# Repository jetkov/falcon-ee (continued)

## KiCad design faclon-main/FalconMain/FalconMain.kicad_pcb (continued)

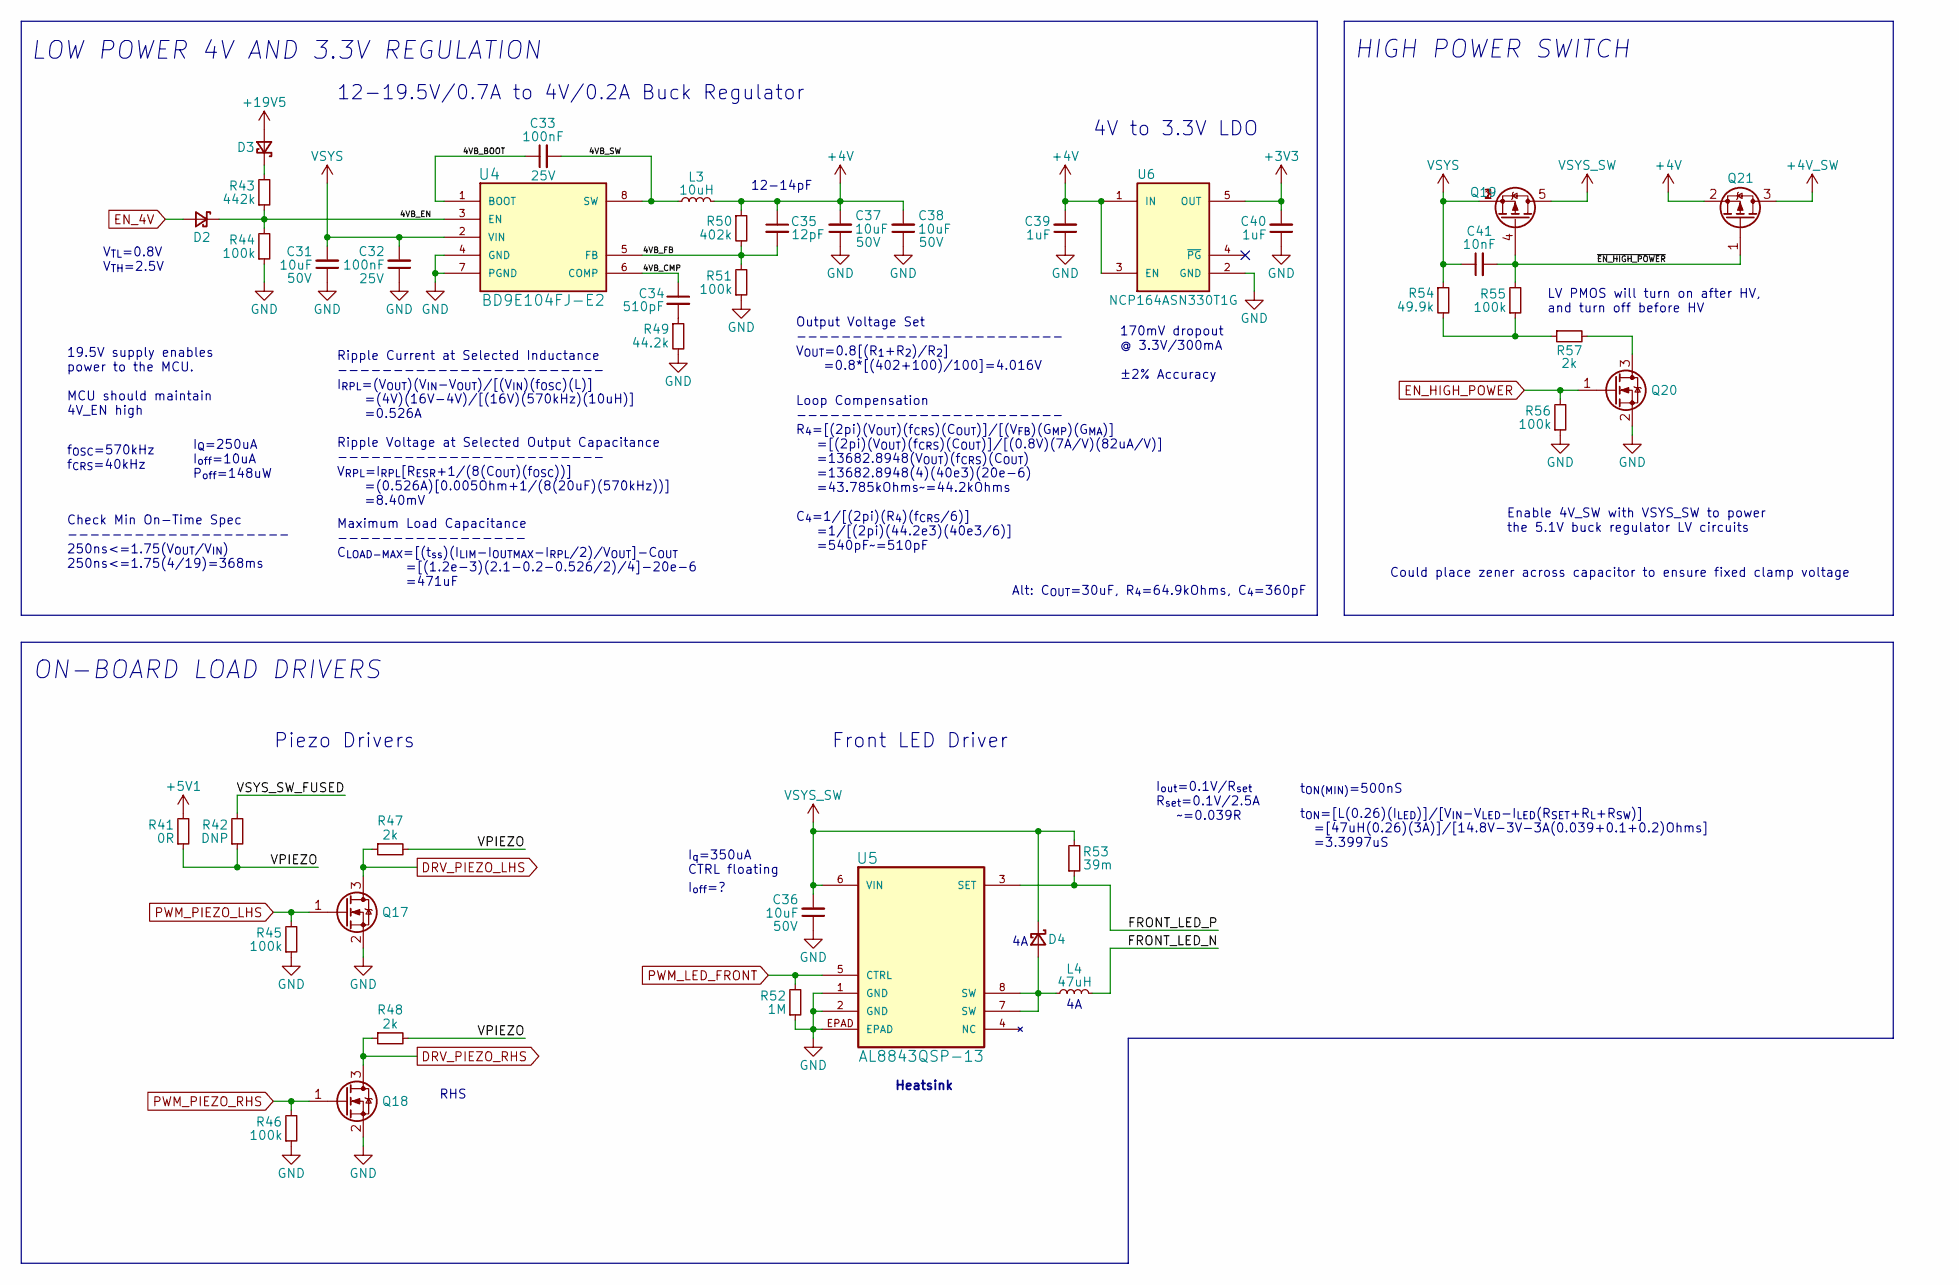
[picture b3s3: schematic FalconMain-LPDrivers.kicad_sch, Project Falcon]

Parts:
C31, C36, C37, C38: 10uF; C_1210_3225Metric; Tolerance 10%; Voltage 50V; Part Number CGA6P3X7S1H106K250AB
C32, C33: 100nF; C_0402_1005Metric; Tolerance 10%; Voltage 25V; Part Number GRM155R71E104KE14D
C34: 510pF; C_0402_1005Metric; Tolerance 5%; Voltage 50V; Part Number GRM1555C1H511JA01D
C35: 12pF; C_0402_1005Metric; Tolerance 5%; Voltage 50V; Part Number GCM1555C1H120JA16D
C39, C40: 1uF; C_0603_1608Metric; Tolerance 10%; Voltage 25V; Part Number CGA3E1X7R1E105K080AC
C41: 10nF; C_0402_1005Metric; Tolerance 10%; Voltage 50V; Part Number 885012205067
D2, D3: 500mA; SC-76-SOD-323_USC_TSB; Voltage 30V; Part Number CUS551V30,H3F
D4: 20A; TO-252-2-3_DPAK_ST; Voltage 45V; Part Number FERD2045SB-TR
L3: 10uH; L_1008_2520Metric; Tolerance 10%; Part Number LBC2518T100K
L4: 47uH; AMDLA1306S; Tolerance 20%; Part Number AMDLA1306S-470MT
Q17, Q18, Q20: Q_NMOS_GSD; SOT-323_SC-70; Voltage 20Vgs/60Vds/1Vth; Part Number DMN61D9UWQ-13
Q19: Q_PMOS_LFPAK; LFPACK56-S08_SOT669_NXP; Voltage 20Vgs/30Vds/3Vth; Part Number BUK6Y19-30PX
Q21: Q_PMOS_GSD; SC-96_TSMT3_ROM; Voltage 20Vgs/30Vds/2.5Vth; Part Number RQ5E025ATTCL
R41: 0R; R_0402_1005Metric; Tolerance Jumper; Part Number RMCF0402ZT0R00
R42: DNP; R_0402_1005Metric; Tolerance Jumper; Part Number RMCF0402ZT0R00
R43: 442k; R_0402_1005Metric; Tolerance 1%; Part Number RMCF0402FT442K
R44, R45, R46, R51, R55, R56: 100k; R_0402_1005Metric; Tolerance 1%; Part Number RC0402FR-13100KL
R47, R48, R57: 2k; R_0402_1005Metric; Tolerance 1%; Part Number RMCF0402FT2K00
R49: 44.2k; R_0402_1005Metric; Tolerance 1%; Part Number RMCF0402FT44K2
R50: 402k; R_0402_1005Metric; Tolerance 1%; Part Number RMCF0402FT402K
R52: 1M; R_0402_1005Metric; Tolerance 1%; Part Number RMCF0402FT1M00
R53: 39m; R_1206_3216Metric; Tolerance 1%; Part Number KRL1632E-M-R039-F-T5
R54: 49.9k; R_0402_1005Metric; Tolerance 1%; Part Number RMCF0402FT49K9
U4: BD9E104FJ-E2; 8-SOIC_8-SOP-J_ROHM; Part Number BD9E104FJ-E2
U5: AL8843QSP-13; 8-SOIC_SO-8EP_DIO; Part Number AL8843QSP-13
U6: NCP164ASN330T1G; SOT-23-5_TSOP−5_ON; Part Number NCP164ASN330T1G

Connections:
+3V3: C40.2, U6.5 (OUT); also elsewhere on the board
+4V: C35.1, C37.2, C38.2, C39.2, L3.2, Q21.2 (S), R50.1, U6.1 (IN), U6.3 (EN)
+4V_SW: Q21.3 (D); also elsewhere on the board
+5V1: R41.2; also elsewhere on the board
+19V5: D3.2 (A); also elsewhere on the board
/Low Power and Drivers/4VB_BOOT: C33.1, U4.1 (BOOT)
/Low Power and Drivers/4VB_CMP: C34.1, U4.6 (COMP)
/Low Power and Drivers/4VB_EN: D2.1 (K), R43.1, R44.2, U4.3 (EN)
/Low Power and Drivers/4VB_FB: C35.2, R50.2, R51.2, U4.5 (FB)
/Low Power and Drivers/4VB_SW: C33.2, L3.1, U4.8 (SW)
/Low Power and Drivers/FRONT_LED_N: L4.2
/Low Power and Drivers/FRONT_LED_P: R53.1, U5.3 (SET)
/Low Power and Drivers/VPIEZO: R41.1, R42.1, R47.2, R48.2
/Low Power and Drivers/VSYS_SW_FUSED: R42.2
/Low Power and Drivers/~EN_HIGH_POWER: C41.2, Q19.4 (G), Q21.1 (G), R55.2
DRV_PIEZO_LHS: Q17.3 (D), R47.1; also elsewhere on the board
DRV_PIEZO_RHS: Q18.3 (D), R48.1; also elsewhere on the board
EN_4V: D2.2 (A); also elsewhere on the board
EN_HIGH_POWER: Q20.1 (G), R56.2; also elsewhere on the board
GND: C31.1, C32.1, C36.1, C37.1, C38.1, C39.1, C40.1, Q17.2 (S), Q18.2 (S), Q20.2 (S), R44.1, R45.1, R46.1, R49.2, R51.1, R52.1, R56.1, U4.4 (GND), U4.7 (PGND), U5.1 (GND), U5.2 (GND), U5.EPAD, U6.2 (GND); also elsewhere on the board
unnamed: C34.2, R49.1
unnamed: D3.1 (K), R43.2
unnamed: D4.1 (A), D4.2 (A), L4.1, U5.7 (SW), U5.8 (SW)
unnamed: Q20.3 (D), R57.2
unnamed: R54.2, R55.1, R57.1
PWM_LED_FRONT: R52.2, U5.5 (CTRL); also elsewhere on the board
PWM_PIEZO_LHS: Q17.1 (G), R45.2; also elsewhere on the board
PWM_PIEZO_RHS: Q18.1 (G), R46.2; also elsewhere on the board
VSYS: C31.2, C32.2, C41.1, Q19.1 (S), Q19.2 (S), Q19.3 (S), R54.1, U4.2 (VIN); also elsewhere on the board
VSYS_SW: C36.2, D4.3 (K), Q19.5 (D), R53.2, U5.6 (VIN); also elsewhere on the board

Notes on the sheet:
I_{Q}=250uA I_{off}=10uA P_{off}=148uW
Loop Compensation ------------------------ R_{4}=[(2pi)(V_{OUT})(f_{CRS})(C_{OUT})]/[(V_{FB})(G_{MP})(G_{MA})] =[(2pi)(V_{OUT})(f_{CRS})(C_{OUT})]/[(0.8V)(7A/V)(82uA/V)] =13682.8948(V_{OUT})(f_{CRS})(C_{OUT}) =13682.8948(4)(40e3)(20e-6) =43.785kOhms~=44.2kOhms C_{4}=1/[(2pi)(R_{4})(f_{CRS}/6)] =1/[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
HIGH POWER SWITCH
Piezo Drivers
4V to 3.3V LDO
19.5V supply enables power to the MCU. MCU should maintain 4V_EN high
f_{OSC}=570kHz f_{CRS}=40kHz
Maximum Load Capacitance ----------------- C_{LOAD-MAX}=[(t_{ss})(I_{LIM}-I_{OUTMAX}-I_{RPL}/2)/V_{OUT}]-C_{OUT} =[(1.2e-3)(2.1-0.2-0.526/2)/4]-20e-6 =471uF
Ripple Current at Selected Inductance ------------------------ I_{RPL}=(V_{OUT})(V_{IN}-V_{OUT})/[(V_{IN})(f_{OSC})(L)] =(4V)(16V-4V)/[(16V)(570kHz)(10uH)] =0.526A Ripple Voltage at Selected Output Capacitance ------------------------ V_{RPL}=I_{RPL}[R_{ESR}+1/(8(C_{OUT})(f_{OSC}))] =(0.526A)[0.005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
Alt: C_{OUT}=30uF, R_{4}=64.9kOhms, C_{4}=360pF
LV PMOS will turn on after HV, and turn off before HV
Front LED Driver
I_{out}=0.1V/R_{set} R_{set}=0.1V/2.5A ~=0.039R
12-19.5V/0.7A to 4V/0.2A Buck Regulator
12-14pF
RHS
LOW POWER 4V AND 3.3V REGULATION
I_{q}=350uA CTRL floating
Output Voltage Set ------------------------ V_{OUT}=0.8[(R_{1}+R_{2})/R_{2}] =0.8*[(402+100)/100]=4.016V
t_{ON(MIN)}=500nS
I_{off}=?
Could place zener across capacitor to ensure fixed clamp voltage
Enable 4V_SW with VSYS_SW to power the 5.1V buck regulator LV circuits
170mV dropout @ 3.3V/300mA ±2% Accuracy
Check Min On-Time Spec -------------------- 250ns<=1.75(V_{OUT}/V_{IN}) 250ns<=1.75(4/19)=368ms
ON-BOARD LOAD DRIVERS
Heatsink
t_{ON}=[L(0.26)(I_{LED})]/[V_{IN}-V_{LED}-I_{LED}(R_{SET}+R_{L}+R_{SW})] =[47uH(0.26)(3A)]/[14.8V-3V-3A(0.039+0.1+0.2)Ohms] =3.3997uS
V_{TL}=0.8V V_{TH}=2.5V

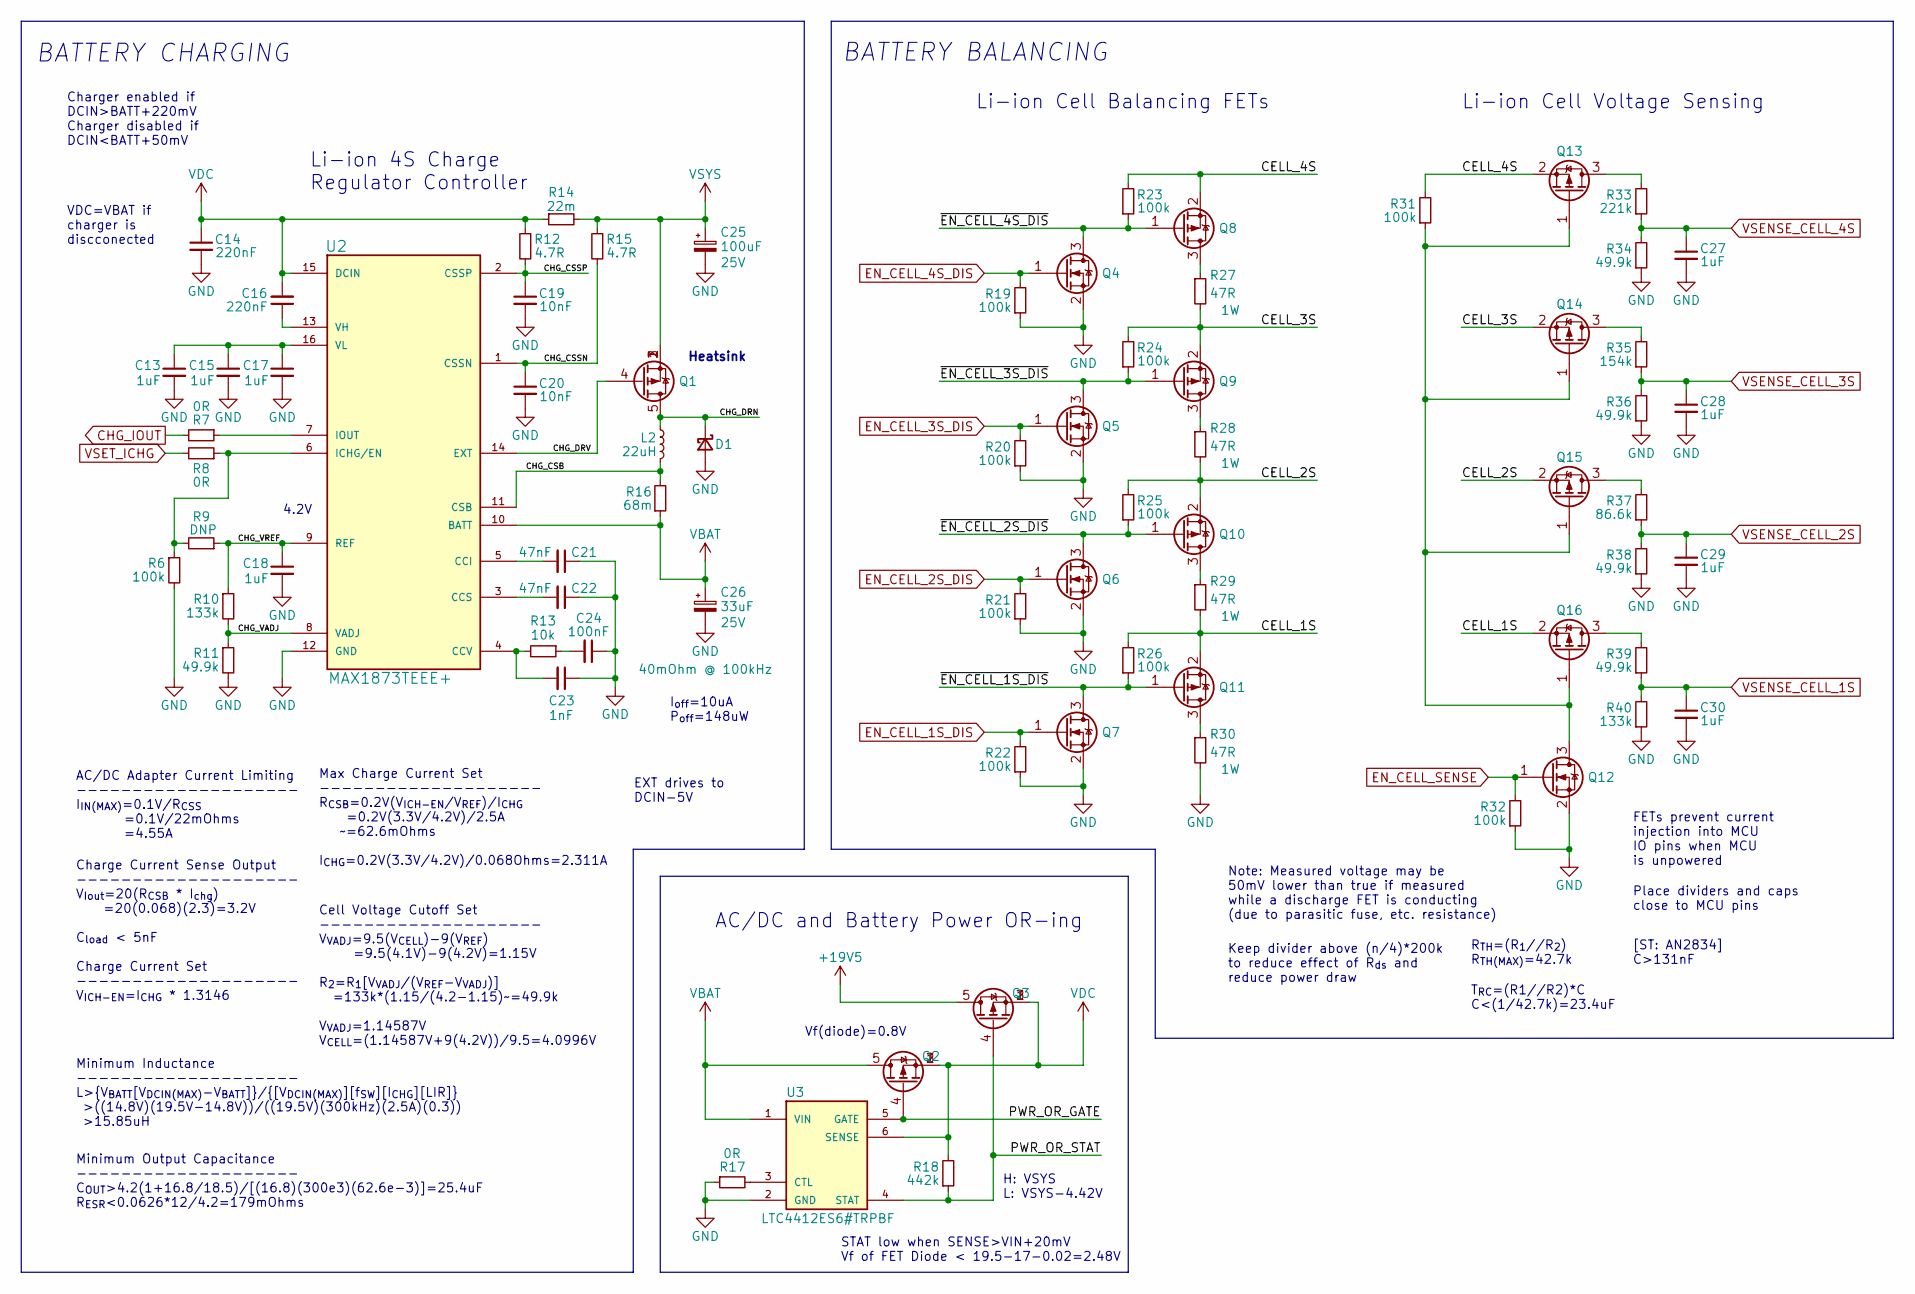
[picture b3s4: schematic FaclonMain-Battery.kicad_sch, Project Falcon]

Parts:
C13, C15, C17, C18, C27, C28, C29, C30: 1uF; C_0603_1608Metric; Tolerance 10%; Voltage 25V; Part Number CGA3E1X7R1E105K080AC
C14, C16: 220nF; C_0603_1608Metric; Tolerance 10%; Voltage 50V; Part Number C1608X7R1H224K080AB
C19, C20: 10nF; C_0402_1005Metric; Tolerance 10%; Voltage 50V; Part Number 885012205067
C21, C22: 47nF; C_0402_1005Metric; Tolerance 10%; Voltage 50V; Part Number GRM155R71H473KE14D
C23: 1nF; C_0402_1005Metric; Tolerance 10%; Voltage 50V; Part Number 885012205061
C24: 100nF; C_0402_1005Metric; Tolerance 10%; Voltage 25V; Part Number GRM155R71E104KE14D
C25: 100uF; CP_Radial_D8.0mm_P3.50mm; Tolerance 20%; Voltage 25V; Part Number A759KS107M1EAAE025
C26: 33uF; CP_Radial_D6.3mm_P2.50mm; Tolerance 20%; Voltage 25V; Part Number A758EK336M1EAAE040
D1: 20A; TO-252-2-3_DPAK_ST; Voltage 45V; Part Number FERD2045SB-TR
L2: 22uH; DR125-220-R_Handsolder; Tolerance 20%; Part Number DR125-220-R
Q1, Q2, Q3: Q_PMOS_LFPAK; LFPACK56-S08_SOT669_NXP; Voltage 20Vgs/30Vds/3Vth; Part Number BUK6Y19-30PX
Q4, Q5, Q6, Q7, Q12: Q_NMOS_GSD; SOT-323_SC-70; Voltage 20Vgs/60Vds/1Vth; Part Number DMN61D9UWQ-13
Q8, Q9, Q10, Q11, Q13, Q14, Q15, Q16: Q_PMOS_GSD; SC-96_TSMT3_ROM; Voltage 20Vgs/30Vds/2.5Vth; Part Number RQ5E025ATTCL
R6, R19, R20, R21, R22, R23, R24, R25, R26, R31, R32: 100k; R_0402_1005Metric; Tolerance 1%; Part Number RC0402FR-13100KL
R7, R8, R17: 0R; R_0402_1005Metric; Tolerance Jumper; Part Number RMCF0402ZT0R00
R9: DNP; R_0402_1005Metric; Tolerance 1%; Part Number RMCF0402FT27K4
R10, R40: 133k; R_0402_1005Metric; Tolerance 1%; Part Number CR0402-FX-1333GLF
R11, R34, R36, R38, R39: 49.9k; R_0402_1005Metric; Tolerance 1%; Part Number RMCF0402FT49K9
R12, R15: 4.7R; R_0402_1005Metric; Tolerance 1%; Part Number RMCF0402FT4R70
R13: 10k; R_0402_1005Metric; Tolerance 1%; Part Number RMCF0402FT10K0
R14: 22m; R_1206_3216Metric; Tolerance 1%; Part Number KRL1632E-M-R022-F-T5
R16: 68m; R_0612_1632Metric; Tolerance 1%; Part Number LTR18EZPFSR068
R18: 442k; R_0402_1005Metric; Tolerance 1%; Part Number RMCF0402FT442K
R27, R28, R29, R30: 47R; R_2512_6332Metric; Tolerance 5%; Part Number RMCF2512JT47R0
R33: 221k; R_0402_1005Metric; Tolerance 1%; Part Number RMCF0402FT221K
R35: 154k; R_0402_1005Metric; Tolerance 1%; Part Number RMCF0402FT154K
R37: 86.6k; R_0402_1005Metric; Tolerance 1%; Part Number RMCF0402FT86K6
U2: MAX1873TEEE+; 16-SSOP_16-QSOP_MAX; Part Number MAX1873TEEE+
U3: LTC4412ES6#TRPBF; SOT-23-6_TSOT-23-6_LT; Part Number LTC4412ES6#TRPBF

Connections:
+19V5: Q3.5 (D); also elsewhere on the board
/Battery/CELL_1S: Q11.2 (S), Q16.2 (S), R26.2, R29.2
/Battery/CELL_2S: Q10.2 (S), Q15.2 (S), R25.2, R28.2
/Battery/CELL_3S: Q9.2 (S), Q14.2 (S), R24.2, R27.2
/Battery/CELL_4S: Q8.2 (S), Q13.2 (S), R23.2, R31.2
/Battery/CHG_CSB: L2.2, R16.2, U2.11 (CSB)
/Battery/CHG_CSSN: C20.1, R15.2, U2.1 (CSSN)
/Battery/CHG_CSSP: C19.1, R12.2, U2.2 (CSSP)
/Battery/CHG_DRN: D1.3 (K), L2.1, Q1.5 (D)
/Battery/CHG_DRV: Q1.4 (G), U2.14 (EXT)
/Battery/CHG_VADJ: R10.2, R11.1, U2.8 (VADJ)
/Battery/CHG_VREF: C18.1, R9.1, R10.1, U2.9 (REF)
/Battery/PWR_OR_GATE: Q2.4 (G), U3.5 (GATE)
/Battery/PWR_OR_STAT: Q3.4 (G), R18.1, U3.4 (STAT)
/Battery/~EN_CELL_1S_DIS: Q7.3 (D), Q11.1 (G), R26.1
/Battery/~EN_CELL_2S_DIS: Q6.3 (D), Q10.1 (G), R25.1
/Battery/~EN_CELL_3S_DIS: Q5.3 (D), Q9.1 (G), R24.1
/Battery/~EN_CELL_4S_DIS: Q4.3 (D), Q8.1 (G), R23.1
CHG_IOUT: R7.2; also elsewhere on the board
EN_CELL_1S_DIS: Q7.1 (G), R22.2; also elsewhere on the board
EN_CELL_2S_DIS: Q6.1 (G), R21.2; also elsewhere on the board
EN_CELL_3S_DIS: Q5.1 (G), R20.2; also elsewhere on the board
EN_CELL_4S_DIS: Q4.1 (G), R19.2; also elsewhere on the board
EN_CELL_SENSE: Q12.1 (G), R32.2; also elsewhere on the board
GND: C13.2, C14.2, C15.2, C17.2, C18.2, C19.2, C20.2, C21.1, C22.1, C23.1, C24.1, C25.2, C26.2, C27.2, C28.2, C29.2, C30.2, D1.1 (A), D1.2 (A), Q4.2 (S), Q5.2 (S), Q6.2 (S), Q7.2 (S), Q12.2 (S), R6.2, R11.2, R17.1, R19.1, R20.1, R21.1, R22.1, R30.2, R32.1, R34.1, R36.1, R38.1, R40.1, U2.12 (GND), U3.2 (GND); also elsewhere on the board
unnamed: C13.1, C15.1, C17.1, U2.16 (VL)
unnamed: C16.1, U2.13 (VH)
unnamed: C21.2, U2.5 (CCI)
unnamed: C22.2, U2.3 (CCS)
unnamed: C23.2, R13.2, U2.4 (CCV)
unnamed: C24.2, R13.1
unnamed: Q8.3 (D), R27.1
unnamed: Q9.3 (D), R28.1
unnamed: Q10.3 (D), R29.1
unnamed: Q11.3 (D), R30.1
unnamed: Q12.3 (D), Q13.1 (G), Q14.1 (G), Q15.1 (G), Q16.1 (G), R31.1
unnamed: Q13.3 (D), R33.2
unnamed: Q14.3 (D), R35.2
unnamed: Q15.3 (D), R37.2
unnamed: Q16.3 (D), R39.2
unnamed: R6.1, R8.1, R9.2, U2.6 (ICHG/EN)
unnamed: R7.1, U2.7 (IOUT)
unnamed: R17.2, U3.3 (CTL)
VBAT: C26.1, Q2.5 (D), R16.1, U2.10 (BATT), U3.1 (VIN); also elsewhere on the board
VDC: C14.1, C16.2, Q2.1 (S), Q2.2 (S), Q2.3 (S), Q3.1 (S), Q3.2 (S), Q3.3 (S), R12.1, R14.1, R18.2, U2.15 (DCIN), U3.6 (SENSE)
VSENSE_CELL_1S: C30.1, R39.1, R40.2; also elsewhere on the board
VSENSE_CELL_2S: C29.1, R37.1, R38.2; also elsewhere on the board
VSENSE_CELL_3S: C28.1, R35.1, R36.2; also elsewhere on the board
VSENSE_CELL_4S: C27.1, R33.1, R34.2; also elsewhere on the board
VSET_ICHG: R8.2; also elsewhere on the board
VSYS: C25.1, Q1.1 (S), Q1.2 (S), Q1.3 (S), R14.2, R15.1; also elsewhere on the board

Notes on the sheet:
STAT low when SENSE>VIN+20mV Vf of FET Diode < 19.5-17-0.02=2.48V
Cell Voltage Cutoff Set -------------------- V_{VADJ}=9.5(V_{CELL})-9(V_{REF}) =9.5(4.1V)-9(4.2V)=1.15V R_{2}=R_{1}[V_{VADJ}/(V_{REF}-V_{VADJ})] =133k*(1.15/(4.2-1.15)~=49.9k V_{VADJ}=1.14587V V_{CELL}=(1.14587V+9(4.2V))/9.5=4.0996V
4.2V
EXT drives to DCIN-5V
Charger enabled if DCIN>BATT+220mV Charger disabled if DCIN<BATT+50mV
Keep divider above (n/4)*200k to reduce effect of R_{ds} and reduce power draw
FETs prevent current injection into MCU IO pins when MCU is unpowered
Note: Measured voltage may be 50mV lower than true if measured while a discharge FET is conducting (due to parasitic fuse, etc. resistance)
T_{RC}=(R1//R2)*C C<(1/42.7k)=23.4uF
Max Charge Current Set -------------------- R_{CSB}=0.2V(V_{ICH-EN}/V_{REF})/I_{CHG} =0.2V(3.3V/4.2V)/2.5A ~=62.6mOhms I_{CHG}=0.2V(3.3V/4.2V)/0.068Ohms=2.311A
BATTERY BALANCING
Minimum Output Capacitance -------------------- C_{OUT}>4.2(1+16.8/18.5)/[(16.8)(300e3)(62.6e-3)]=25.4uF R_{ESR}<0.0626*12/4.2=179mOhms
AC/DC and Battery Power OR-ing
R_{TH}=(R_{1}//R_{2}) R_{TH(MAX)}=42.7k
[ST: AN2834] C>131nF
Li-ion Cell Balancing FETs
Heatsink
I_{off}=10uA P_{off}=148uW
AC/DC Adapter Current Limiting -------------------- I_{IN(MAX)}=0.1V/R_{CSS} =0.1V/22mOhms =4.55A
Li-ion Cell Voltage Sensing
BATTERY CHARGING
Minimum Inductance -------------------- L>{V_{BATT}[V_{DCIN(MAX)}-V_{BATT}]}/{[V_{DCIN(MAX)}][f_{SW}][I_{CHG}][LIR]} >((14.8V)(19.5V-14.8V))/((19.5V)(300kHz)(2.5A)(0.3)) >15.85uH
Charge Current Sense Output -------------------- V_{Iout}=20(R_{CSB} * I_{chg}) =20(0.068)(2.3)=3.2V C_{load} < 5nF Charge Current Set -------------------- V_{ICH-EN}=I_{CHG} * 1.3146
Place dividers and caps close to MCU pins
Vf(diode)=0.8V
Li-ion 4S Charge Regulator Controller
H: VSYS L: VSYS-4.42V
VDC=VBAT if charger is discconected

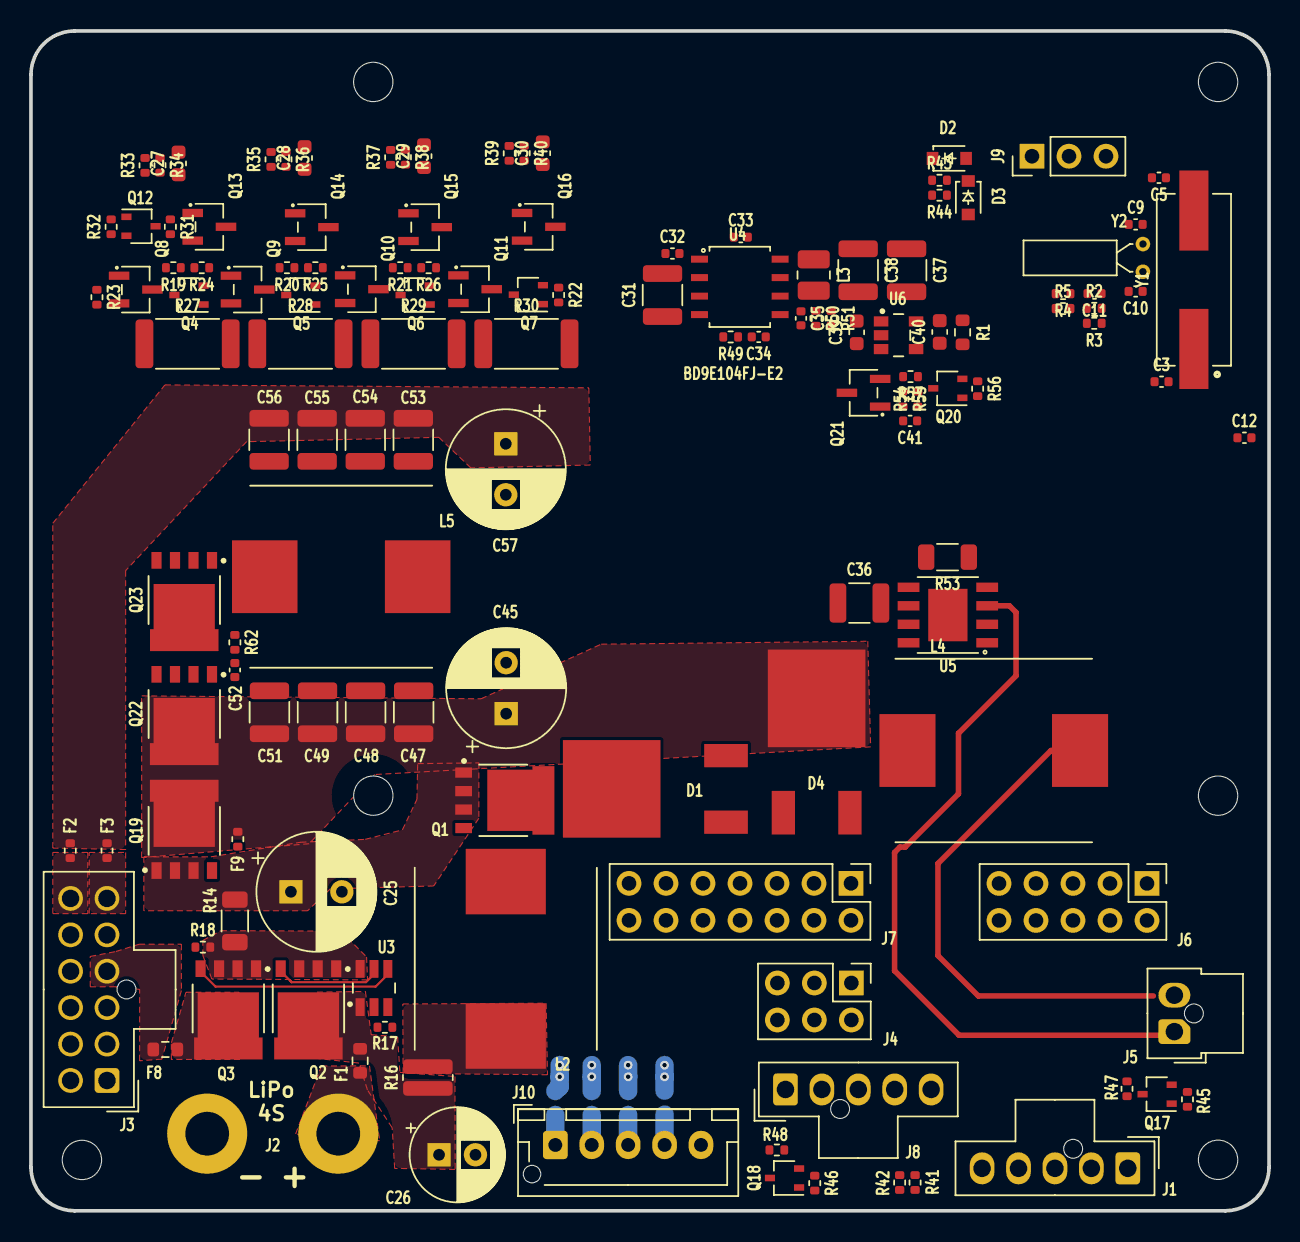
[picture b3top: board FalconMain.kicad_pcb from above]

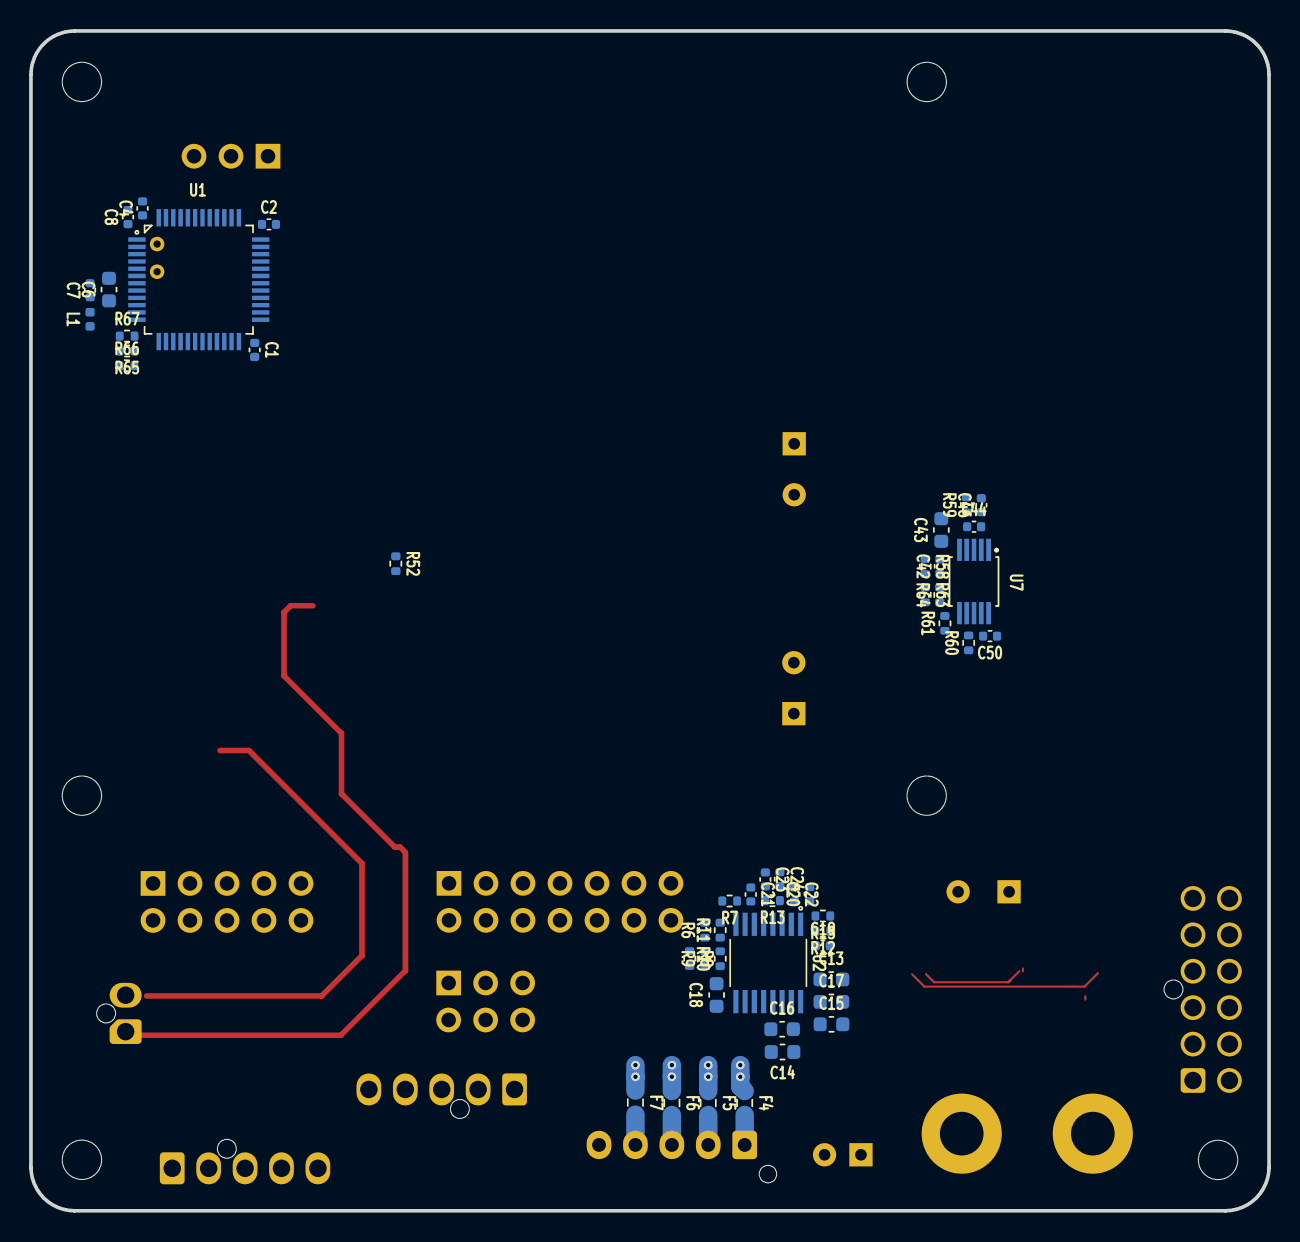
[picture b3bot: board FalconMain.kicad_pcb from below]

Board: 4 copper layers, 85.0 x 81.0 mm, 190 parts (50 on the bottom side), 123 nets.

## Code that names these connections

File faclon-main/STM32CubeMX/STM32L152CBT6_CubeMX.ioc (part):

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Mcu.Name=STM32L152C(6-8-B)Tx
Mcu.Package=LQFP48
Mcu.UserName=STM32L152CBTx
PA0-WKUP1.GPIOParameters=GPIO_Label
PA0-WKUP1.GPIO_Label=SPR_ADC_IN0
PA0-WKUP1.Mode=IN0
PA0-WKUP1.Signal=ADC_IN0
PA1.GPIOParameters=GPIO_Label
PA1.GPIO_Label=VSENSE_5V1
PA1.Mode=IN1
PA1.Signal=ADC_IN1
PA10.Mode=Asynchronous
PA10.Signal=USART1_RX
PA11.Mode=CTS_RTS
PA11.Signal=USART1_CTS
PA12.Mode=CTS_RTS
PA12.Signal=USART1_RTS
PA13.Mode=Serial_Wire
PA13.Signal=SYS_JTMS-SWDIO
PA14.Mode=Serial_Wire
PA14.Signal=SYS_JTCK-SWCLK
PA15.Mode=NSS_Signal_Hard_Input
PA15.Signal=SPI1_NSS
PA2.GPIOParameters=GPIO_Label
PA2.GPIO_Label=PWM_LED_LHS
PA2.Signal=S_TIM2_CH3
PA3.GPIOParameters=GPIO_Label
PA3.GPIO_Label=PWM_LED_RHS
PA3.Signal=S_TIM2_CH4
PA4.GPIOParameters=GPIO_Label
PA4.GPIO_Label=ICHG_EN
PA4.Signal=COMP_DAC1_group
PA5.Mode=Full_Duplex_Slave
PA5.Signal=SPI1_SCK
PA6.GPIOParameters=GPIO_Label
PA6.GPIO_Label=PWM_LED_REAR_1
PA6.Signal=S_TIM3_CH1
PA7.GPIOParameters=GPIO_Label
PA7.GPIO_Label=PWM_LED_REAR_2
PA7.Signal=S_TIM3_CH2
PA8.GPIOParameters=GPIO_Label
PA8.GPIO_Label=GPIO_SPR
PA8.Signal=GPIO_Output
PA9.Mode=Asynchronous
PA9.Signal=USART1_TX
PB0.GPIOParameters=GPIO_Label
PB0.GPIO_Label=VSENSE_CELL_1S
PB0.Mode=IN8
PB0.Signal=ADC_IN8
PB1.GPIOParameters=GPIO_Label
PB1.GPIO_Label=VSENSE_CELL_2S
PB1.Mode=IN9
PB1.Signal=ADC_IN9
PB10.GPIOParameters=GPIO_Label
PB10.GPIO_Label=CELL_2S_DIS_EN
PB10.Signal=GPIO_Output
PB11.GPIOParameters=GPIO_Label
PB11.GPIO_Label=CELL_3S_DIS_EN
PB11.Signal=GPIO_Output
PB12.GPIOParameters=GPIO_Label
PB12.GPIO_Label=VSENSE_CELL_3S
PB12.Mode=IN18
PB12.Signal=ADC_IN18
PB13.GPIOParameters=GPIO_Label
PB13.GPIO_Label=VSENSE_CELL_4S
PB13.Mode=IN19
PB13.Signal=ADC_IN19
PB14.GPIOParameters=GPIO_Label
PB14.GPIO_Label=CELL_4S_DIS_EN
PB14.Signal=GPIO_Output
PB15.GPIOParameters=GPIO_Label
PB15.GPIO_Label=PWM_PIEZO_RHS
PB15.Signal=S_TIM11_CH1
PB2.GPIOParameters=GPIO_Label
PB2.GPIO_Label=CELL_1S_DIS_EN
PB2.Signal=GPIO_Output
PB3.GPIOParameters=GPIO_Label
PB3.GPIO_Label=PWM_LED_FRONT
PB3.Signal=S_TIM2_CH2
PB4.Mode=Full_Duplex_Slave
PB4.Signal=SPI1_MISO
PB5.Mode=Full_Duplex_Slave
PB5.Signal=SPI1_MOSI
PB6.GPIOParameters=GPIO_Label
PB6.GPIO_Label=EN_3V5
PB6.Signal=GPIO_Output
PB7.GPIOParameters=GPIO_Label
PB7.GPIO_Label=EN_5V1
PB7.Signal=GPIO_Output
PB8.GPIOParameters=GPIO_Label
PB8.GPIO_Label=PWM_PIEZO_LHS
PB8.Signal=S_TIM10_CH1
PB9.GPIOParameters=GPIO_Label
PB9.GPIO_Label=PWM_SPR
PB9.Signal=S_TIM4_CH4
PC14-OSC32_IN.Mode=LSE-External-Oscillator
PC14-OSC32_IN.Signal=RCC_OSC32_IN
PC15-OSC32_OUT.Mode=LSE-External-Oscillator
PC15-OSC32_OUT.Signal=RCC_OSC32_OUT
PH0-OSC_IN.Mode=HSE-External-Oscillator
PH0-OSC_IN.Signal=RCC_OSC_IN
PH1-OSC_OUT.Mode=HSE-External-Oscillator
PH1-OSC_OUT.Signal=RCC_OSC_OUT
RCC.HSE_VALUE=24000000
RCC.SYSCLKFreq_VALUE=2097000
board=custom

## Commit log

2021-12-31 Init project
2021-12-31 Init lib
2022-01-09 Start
2022-01-10 More final MCU pinout definition
2022-01-10 Add more main board core components
    Charger, LP buck, LiPo conns, piezo drivers, lighting driver and conns
2022-01-10 Remove backups from git
2022-01-15 Fix some pinout things
2022-01-15 More component selection
2022-01-16 Cell vsense WIP
2022-01-19 Define connectors
2022-01-20 Select components, last power design wip
2022-01-21 Commit before 5V buck change
2022-01-21 New buck controller WIP
2022-01-21 HP buck WIP
2022-01-23 Schematic organization WIP
2022-01-23 Organization and start side project
2022-01-24 Some capacitor selection
2022-01-24 Jelly bean selection WIP
2022-01-26 Select all main board components
2022-01-27 PMOS diode replacement
2022-01-27 Review WIP
2022-01-28 Design freeze maybe
2022-01-28 Finishing up schematics - part footprints
2022-01-30 Add some footprints
2022-02-05 Start PCB
2022-02-05 Reorganize
2022-02-05 Layout WIP
2022-02-09 Large component rough placement
2022-02-09 Rought placement done
2022-02-09 Reviewed again
2022-02-10 Layour WIP
2022-02-10 Add heatsink pads
2022-02-10 Routing WIP
2022-02-11 Main routing almost done
2022-02-11 Fix DRC stuff
2022-02-11 Done routing and layout Needs review
2022-02-11 Start side board layout
2022-02-12 Complete aux board layouts
2022-02-12 Generate LHS fab files
2022-02-12 Generate rear fab files
2022-02-12 Generate RHS fab files
2022-02-12 Generate main fab files
2022-02-12 Improve layer organization
2022-02-12 Fix missing mounting holes
2022-02-12 Add falcon logo
2022-02-12 Fill all layers
2022-02-12 Adjust fills
2022-02-12 Fix silk
2022-02-12 Regen RHS fab files
2022-02-16 Sent to PCBWay
